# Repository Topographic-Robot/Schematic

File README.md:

# Schematic
The Robots Schematic, the CAD files can be found in its own repo

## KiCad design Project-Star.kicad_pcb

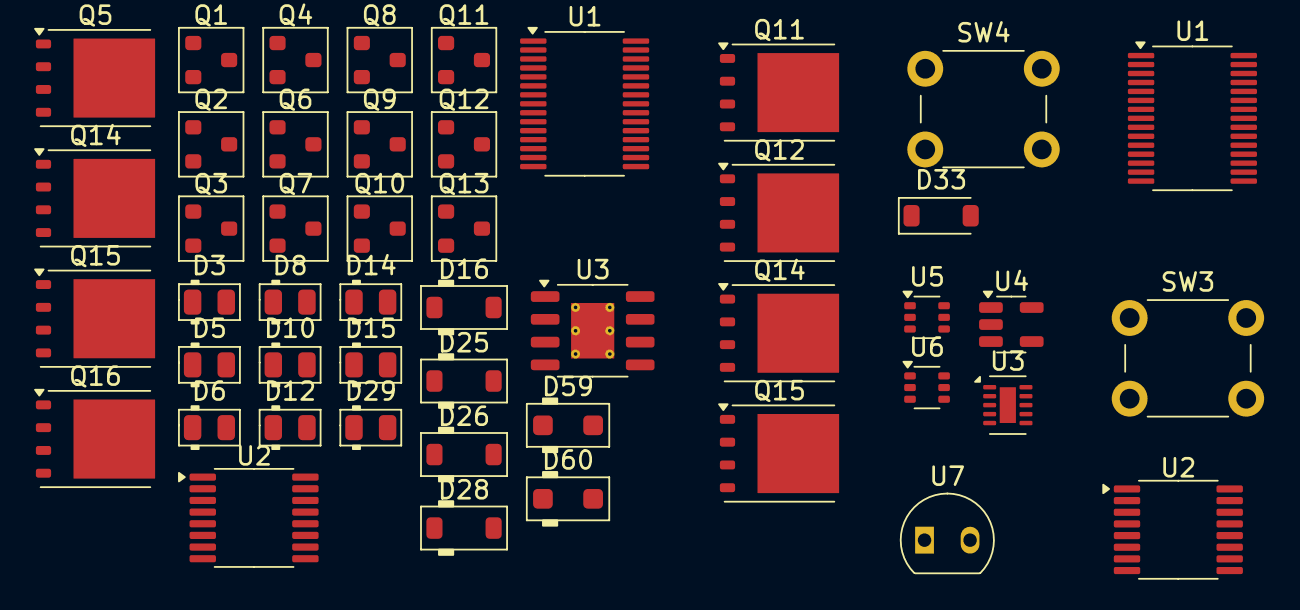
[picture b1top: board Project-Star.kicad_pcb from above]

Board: 2 copper layers, 48 parts (0 on the bottom side), 45 nets, no tracks yet.

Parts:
D3, D5, D6, D8, D10, D12, D14, D15, D29: LED; D_0805_2012Metric
D16, D25, D26, D28: 1N4148W; D_SOD-123
D33: MBR0520LT; D_SOD-123
D59, D60: PTVS40VS1UTR; D_SOD-123F
Q1, Q2, Q3, Q4, Q6, Q7, Q8, Q9: DMN2004K; SOT-23
Q5, Q11#2, Q12, Q14, Q14#2, Q15, Q15#2, Q16: CSD19531Q5A; TDSON-8-1
Q10, Q11, Q13: ZXMP10A13F; SOT-23
Q12#2: BSS123; SOT-23
SW3, SW4: Push_Button; SW_PUSH_6mm
U1, U1#2: BQ7693006DBTR; TSSOP-30_4.4x7.8mm_P0.5mm
U2, U2#2: BQ76200PW; TSSOP-16_4.4x5mm_P0.65mm
U3: MAX17502EATB+T; TDFN-10-1EP_2x3mm_P0.5mm_EP0.9x2mm
U3#2: LM5164DDA; HSOP-8-1EP_3.9x4.9mm_P1.27mm_EP2.41x3.1mm_ThermalVias
U4: TLV75733PDBV; SOT-23-5
U5, U6: LM66100DCKR; SOT-363_SC-70-6
U7: LMT01LPG; TO-92-2

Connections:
+BATT: Q11#2.1 (S), Q11#2.2 (S), Q11#2.3 (S)
/BAT: D16.1 (K), U1.15 (BAT)
/BATT+: Q12.1 (S), Q12.2 (S), Q12.3 (S), U3.2 (VIN)
/BMS Protection Board/CAP2: U1#2.11 (NC(CAP2)), U1#2.12 (NC(CAP2)), U1#2.14 (CAP2)
/BMS Protection Board/TS1: SW3.2, U1#2.6 (TS1)
/BMS Protection Board/VC3: U1#2.23 (VC4), U1#2.24 (VC3)
/BMS Protection Board/VC7: U1#2.17 (VC9), U1#2.18 (VC8)
/C1: D3.2, Q2.2 (S)
/C2: D5.2, Q3.2 (S)
/C3: D6.2, Q4.2 (S)
/C5: D10.2, Q9.2 (S)
/C6: D15.2, Q8.2 (S)
/C7: D14.2, Q7.2 (S)
/C8: D12.2, Q11.2 (S)
/CAP2: U1.11 (NC(CAP2)), U1.12 (NC(CAP2)), U1.14 (CAP2)
/PACK+: Q14#2.1 (S), Q14#2.2 (S), Q14#2.3 (S), Q15#2.1 (S), Q15#2.2 (S), Q15#2.3 (S)
/PCHG: Q10.1 (G), U2#2.14 (PCHG)
/Power Management System Controller/P3V3: D33.1 (K), U5.6 (VOUT), U6.6 (VOUT)
/Power Management System Controller/TIVA_USB-C_5V: U4.1 (IN), U4.3 (EN)
/TS1: D26.1 (K), U1.6 (TS1)
/VC3: U1.23 (VC4), U1.24 (VC3)
/VC4: D25.2 (A), U1.22 (VC5)
/VC5X: D25.1 (K), U1.10 (VC5X)
/VC7: U1.17 (VC9), U1.18 (VC8)
/VC8: D16.2 (A), U1.16 (VC10)
BATT+: D59.1 (K), Q5.1 (S), Q5.2 (S), Q5.3 (S), Q14.1 (S), Q14.2 (S), Q14.3 (S)
GND: D29.1, Q12#2.2 (S), SW4.2, U1.3 (VSS), U1#2.3 (VSS), U2.7 (PMON_EN), U2.9 (VSS), U2#2.7 (PMON_EN), U2#2.9 (VSS), U3.1 (PGND), U3.9 (GND), U3.11 (GND), U3#2.1 (GND), U3#2.9 (EP), U4.2 (GND), U5.2 (GND), U6.2 (GND)
unnamed: D26.2 (A), D28.1 (K)
unnamed: Q5.5 (D), Q10.2 (S), Q14.5 (D), Q15.5 (D), Q16.5 (D)
unnamed: Q11.3 (D), Q11#2.5 (D), Q12.5 (D), Q14#2.5 (D), Q15#2.5 (D), U3#2.2 (VIN), U3#2.3 (EN/UVLO)
unnamed: Q14.4 (G), Q14#2.4 (G)
unnamed: Q15.4 (G), Q15#2.4 (G)
unnamed: U1.30 (ALERT), U1#2.30 (ALERT)
unnamed: U2.16 (CHG), U2#2.16 (CHG)
unnamed: U2.4 (CHG_EN), U2#2.4 (CHG_EN)
unnamed: U2.5 (CP_EN), U2#2.5 (CP_EN)
unnamed: U2.12 (DSG), U2#2.12 (DSG)
unnamed: U2.6 (DSG_EN), U2#2.6 (DSG_EN)
unnamed: U2.11 (PACK), U2#2.11 (PACK)
unnamed: U2.8 (PCHG_EN), U2#2.8 (PCHG_EN)
unnamed: U2.1 (VDDCP), U2#2.1 (VDDCP)
unnamed: U3.5 (FB/VO), U5.1 (VIN)
unnamed: U4.5 (OUT), U5.3 (~CE), U6.1 (VIN)
unnamed: U5.5 (ST), U6.3 (~CE)
PACK+: D60.1 (K), Q13.2 (S), Q15.1 (S), Q15.2 (S), Q15.3 (S), Q16.1 (S), Q16.2 (S), Q16.3 (S)

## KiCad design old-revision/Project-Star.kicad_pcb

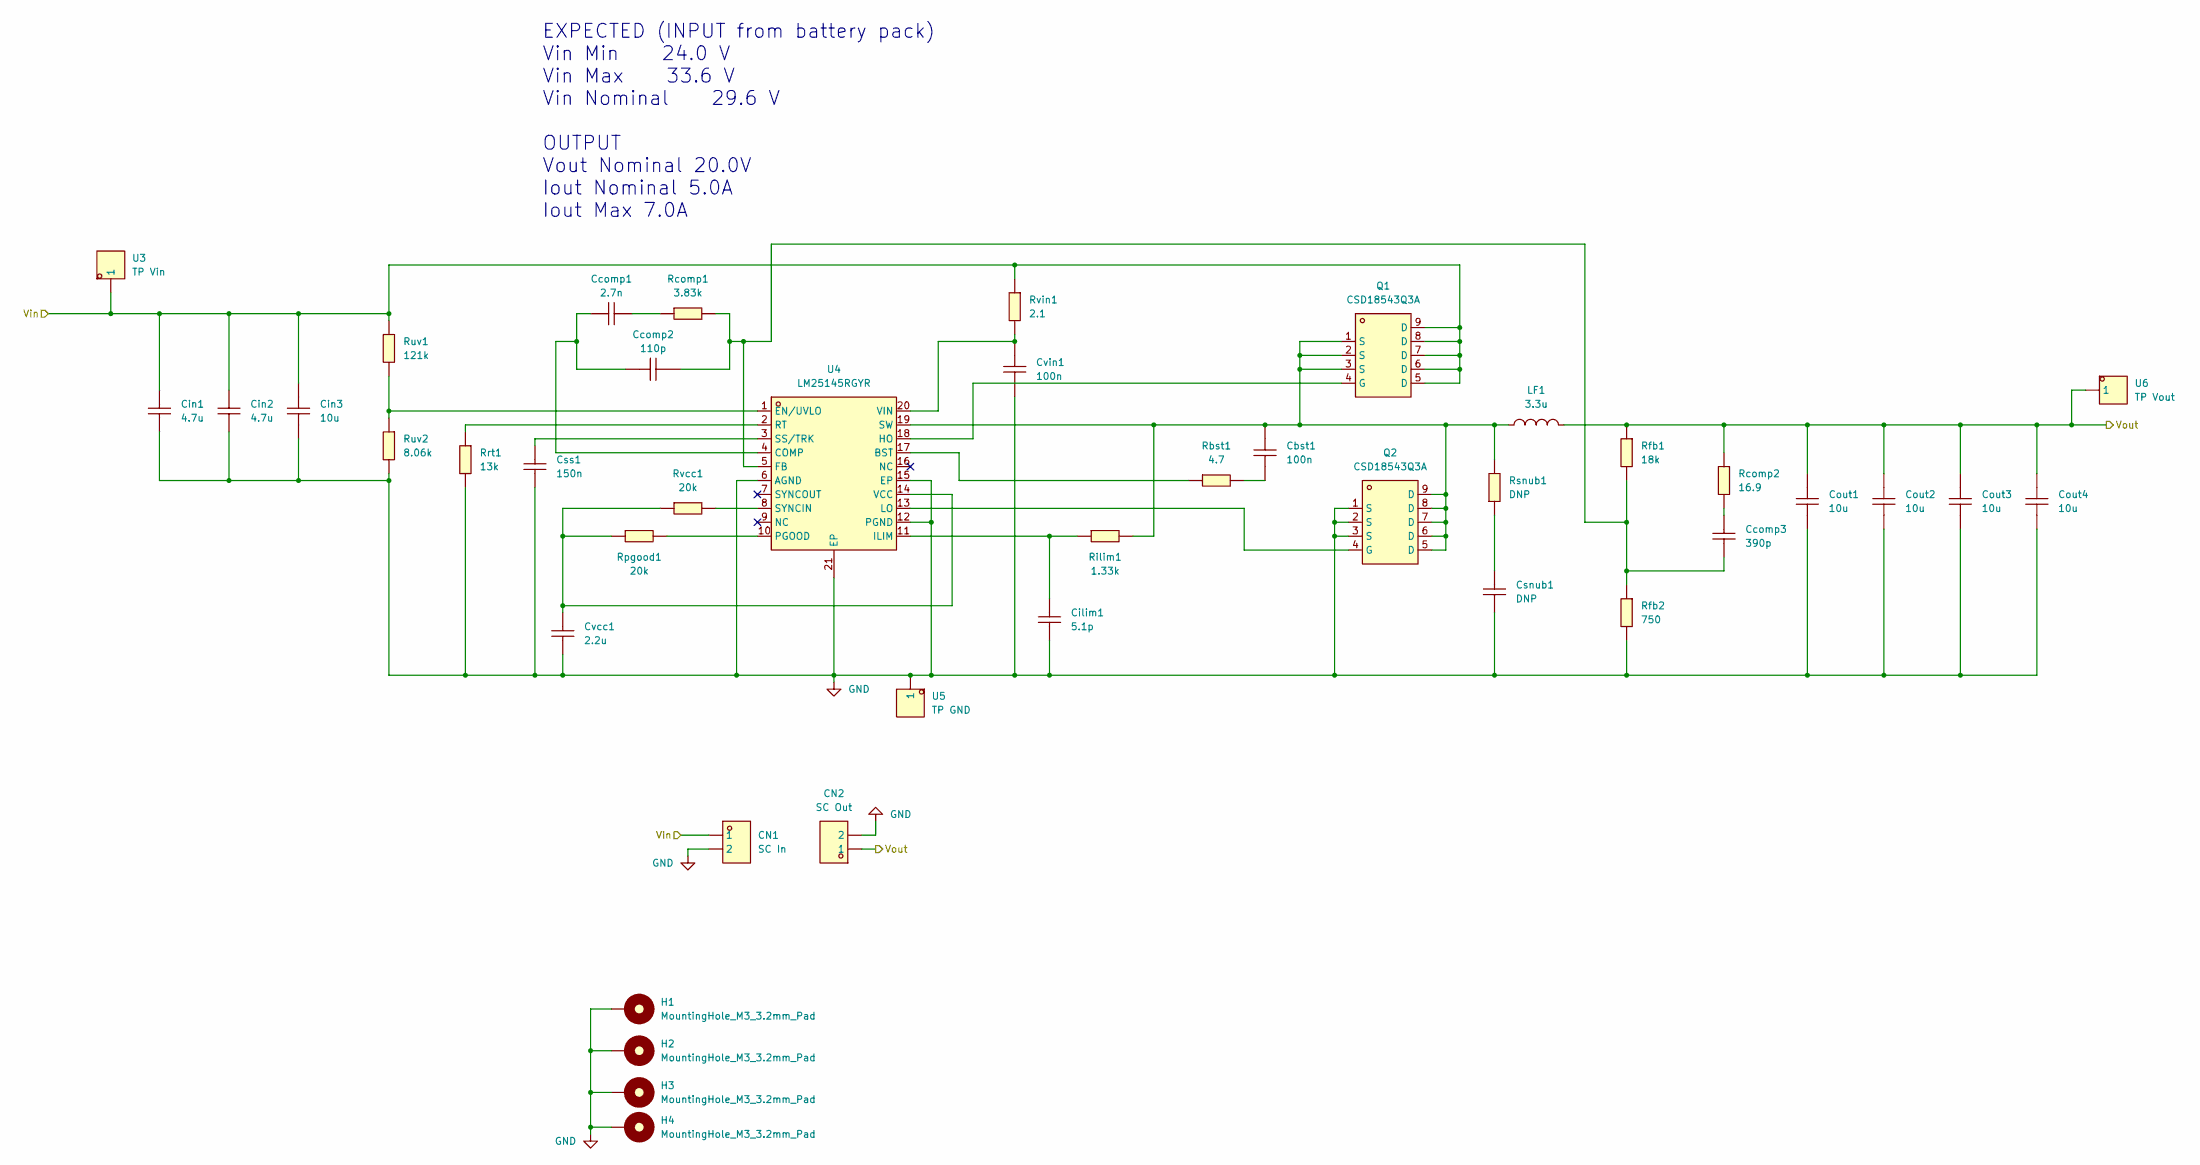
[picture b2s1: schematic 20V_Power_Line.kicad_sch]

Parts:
CN1: SC In; CONN-TH_2P-P5.08_DIBO_DB128V-5.08; LCSC Part C2915639
CN2: SC Out; CONN-TH_2P-P5.08_DIBO_DB128V-5.08; LCSC Part C2915639
Cbst1: 100n; C0603; LCSC Part C14663
Ccomp1: 2.7n; C0603; LCSC Part C1609
Ccomp2: 110p; C0402; LCSC Part C185562
Ccomp3: 390p; C0603; LCSC Part C1617
Cilim1: 5.1p; C0402; LCSC Part C60220
Cin1, Cin2: 4.7u; C1206; LCSC Part C29823
Cin3: 10u; C0805; LCSC Part C440198
Cout1, Cout2, Cout3, Cout4: 10u; C0805; LCSC Part C440198
Csnub1: DNP; C0402; LCSC Part DNP
Css1: 150n; C0603; LCSC Part C1597
Cvcc1: 2.2u; C1206; LCSC Part C50254
Cvin1: 100n; C0603; LCSC Part C14663
H1, H2, H3, H4: MountingHole_M3_3.2mm_Pad; MountingHole_3.2mm_Pad
LF1: 3.3u; IND-SMD_L13.8-W12.8; LCSC Part C19268654
Q1, Q2: CSD18543Q3A; VSONP-8_L3.1-W3.1-P0.65-LS3.5-BL; LCSC Part C840100
Rbst1: 4.7; R0805; LCSC Part C17675
Rcomp1: 3.83k; R0402; LCSC Part C67236
Rcomp2: 16.9; R0402; LCSC Part C82287
Rfb1: 18k; R0603; LCSC Part C25810
Rfb2: 750; R0402; LCSC Part C137842
Rilim1: 1.33k; R0603; LCSC Part C137778
Rpgood1: 20k; R0603; LCSC Part C4184
Rrt1: 13k; R0603; LCSC Part C22797
Rsnub1: DNP; R0805; LCSC Part DNP
Ruv1: 121k; R0402; LCSC Part C11693
Ruv2: 8.06k; R0603; LCSC Part C23112
Rvcc1: 20k; R0603; LCSC Part C4184
Rvin1: 2.1; R0603; LCSC Part C322117
U3: TP Vin; TEST-TH_BD3.17-P1.87; LCSC Part C238127
U4: LM25145RGYR; VQFN-20_L4.5-W3.5-P0.50-BL-EP; LCSC Part C2876740
U5: TP GND; TEST-TH_BD3.17-P1.87; LCSC Part C238127
U6: TP Vout; TEST-TH_BD3.17-P1.87; LCSC Part C238127

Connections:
/20V_Power_Line/Vin: CN1.1, Cin1.1, Cin2.1, Cin3.1, Q1.5 (D), Q1.6 (D), Q1.7 (D), Q1.8 (D), Q1.9 (D), Ruv1.1, Rvin1.1, U3.1; also elsewhere on the board
/20V_Power_Line/Vout: CN2.1, Cout1.1, Cout2.1, Cout3.1, Cout4.1, LF1.2, Rcomp2.1, Rfb1.1, U6.1; also elsewhere on the board
GND: CN1.2, CN2.2, Cilim1.2, Cin1.2, Cin2.2, Cin3.2, Cout1.2, Cout2.2, Cout3.2, Cout4.2, Csnub1.2, Css1.2, Cvcc1.2, Cvin1.2, H1.1, H2.1, H3.1, H4.1, Q2.1 (S), Q2.2 (S), Q2.3 (S), Rfb2.2, Rrt1.2, Ruv2.2, U4.6 (AGND), U4.12 (PGND), U4.15 (EP), U4.21 (EP), U5.1; also elsewhere on the board
unnamed: Cbst1.2, Rbst1.2
unnamed: Ccomp1.2, Rcomp1.1
unnamed: Ccomp3.1, Rcomp2.2
unnamed: Csnub1.1, Rsnub1.1
unnamed: Q1.4 (G), U4.18 (HO)
unnamed: Q2.4 (G), U4.13 (LO)
unnamed: Rbst1.1, U4.17 (BST)
unnamed: Ccomp1.1, Ccomp2.1, U4.4 (COMP)
unnamed: Ruv1.2, Ruv2.1, U4.1 (EN/UVLO)
unnamed: Ccomp2.2, Ccomp3.2, Rcomp1.2, Rfb1.2, Rfb2.1, U4.5 (FB)
unnamed: Cilim1.1, Rilim1.1, U4.11 (ILIM)
unnamed: Rpgood1.2, U4.10 (PGOOD)
unnamed: Rrt1.1, U4.2 (RT)
unnamed: Css1.1, U4.3 (SS/TRK)
unnamed: Cbst1.1, LF1.1, Q1.1 (S), Q1.2 (S), Q1.3 (S), Q2.5 (D), Q2.6 (D), Q2.7 (D), Q2.8 (D), Q2.9 (D), Rilim1.2, Rsnub1.2, U4.19 (SW)
unnamed: Rvcc1.2, U4.8 (SYNCIN)
unnamed: Cvcc1.1, Rpgood1.1, Rvcc1.1, U4.14 (VCC)
unnamed: Cvin1.1, Rvin1.2, U4.20 (VIN)

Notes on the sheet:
EXPECTED (INPUT from battery pack) Vin Min 24.0 V Vin Max 33.6 V Vin Nominal 29.6 V OUTPUT Vout Nominal 20.0V Iout Nominal 5.0A Iout Max 7.0A

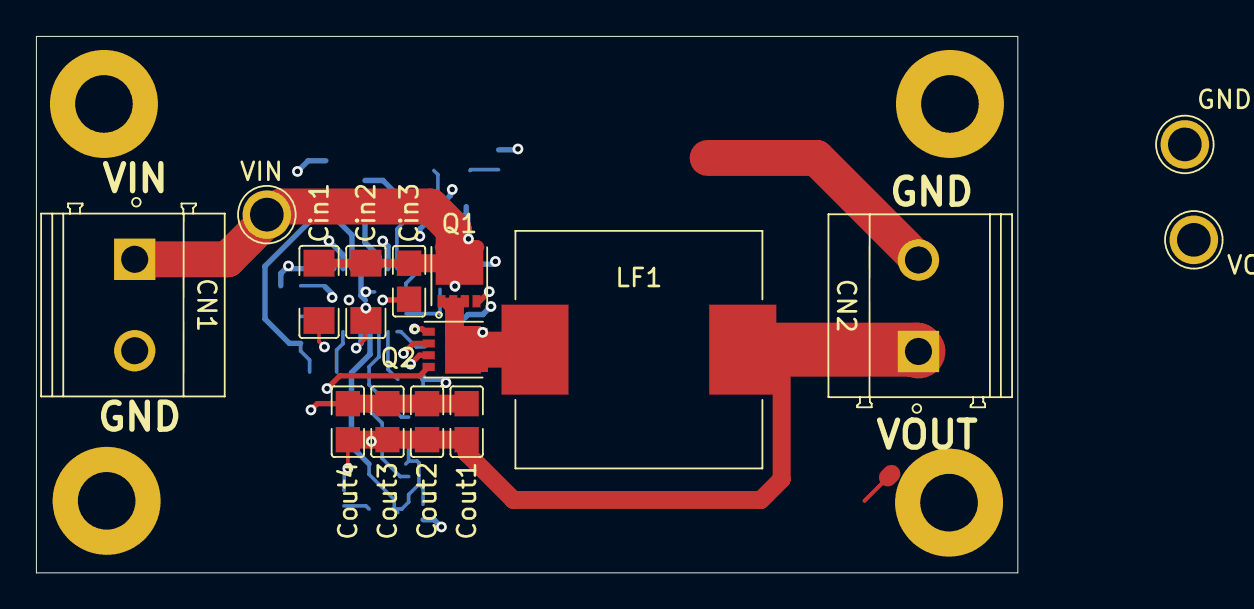
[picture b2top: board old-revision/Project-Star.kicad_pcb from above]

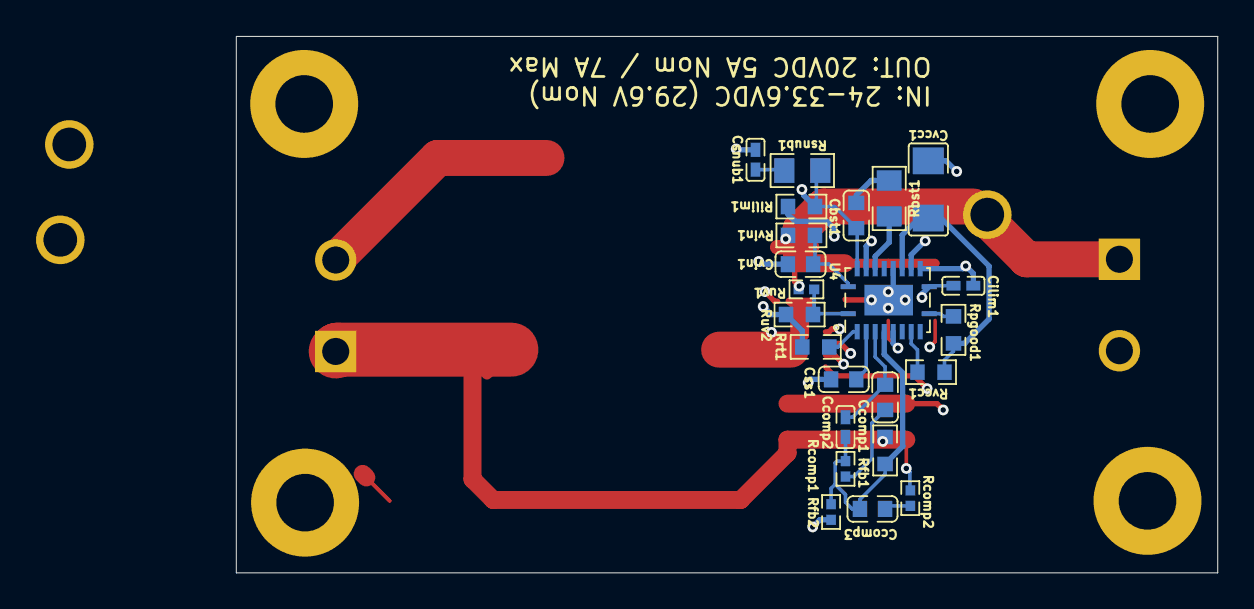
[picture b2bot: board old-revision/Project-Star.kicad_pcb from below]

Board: 4 copper layers, 54.5 x 29.8 mm, 42 parts (23 on the bottom side), 21 nets.

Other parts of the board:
GND: TP GND; TEST-TH_BD3.17-P1.87
VIN: TP Vin; TEST-TH_BD3.17-P1.87
VOUT: TP Vout; TEST-TH_BD3.17-P1.87

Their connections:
/20V_Power_Line/Vin: VIN.1; also elsewhere on the board
/20V_Power_Line/Vout: VOUT.1; also elsewhere on the board
GND: GND.1; also elsewhere on the board

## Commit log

2024-12-15 Power Management
2024-12-15 Movement + Sensors
2024-12-17 THEY ARE QUAD TRISTATE BUFFERS TOOO SOOOOO I GOT 400 TRISTATE BUFFERS!!!!!
2024-12-18 Parallel > USB ?!
2025-04-29 PCA9685
2025-04-29 removed crystal, fixed caps
2025-05-01 added 3v3 line
2025-05-01 added more power lines
2025-05-13 20V line PCB v1
2025-05-13 fixed grounding vias
2025-05-13 20V line V2
2025-05-15 In Progress v3
2025-05-15 20V Line v3
2025-05-23 current progress
2025-05-23 v1 design of bms
2025-05-24 redesign with refernce
2025-05-24 more design info
2025-05-25 datasheets
2025-05-26 cgr, dsg fets + jtag
2025-05-26 need to fix regsrc
2025-06-03 commit before redesign of usb-c
2025-06-04 Restructured Layout
2025-06-11 worked on MCU
2025-07-26 commit before simplifying and removing features
2025-08-02 Added Fuel/Gas Guage
2025-08-02 forgot to give credit to TIDA-00792
2025-08-03 ready to start first pass review on bms
2025-08-03 added schematic as pdf
2025-08-12 I still need to add the 6V line and test points
2025-08-12 Fixed 5V Line
2025-08-21 in progress still
